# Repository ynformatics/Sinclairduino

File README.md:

# Sinclairduino
See https://ynformatics.com/2021/sinclairduino-vintage-sinclair-calculator-reanimated/

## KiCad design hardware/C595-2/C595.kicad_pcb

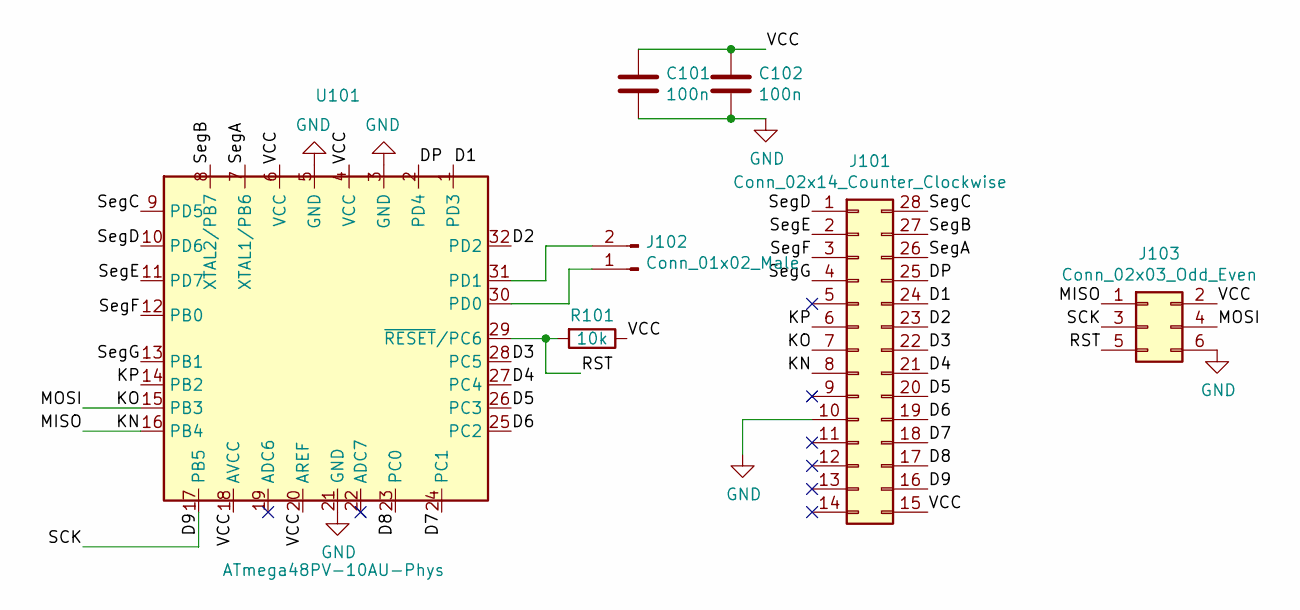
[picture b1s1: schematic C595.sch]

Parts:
C101, C102: 100n; C_0603
J101: Conn_02x14_Counter_Clockwise; DIP-28_W15.24mm
J102: Conn_01x02_Male; C_0805
J103: Conn_02x03_Odd_Even; Pin_Header_Straight_2x03_Pitch1.27mm_SMD
R101: 10k; R_0603
U101: ATmega48PV-10AU-Phys; TQFP-32_7x7mm_Pitch0.8mm

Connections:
/D1: J101.24, U101.1 (PD3)
/D2: J101.23, U101.32 (PD2)
/D3: J101.22, U101.28 (PC5)
/D4: J101.21, U101.27 (PC4)
/D5: J101.20, U101.26 (PC3)
/D6: J101.19, U101.25 (PC2)
/D7: J101.18, U101.24 (PC1)
/D8: J101.17, U101.23 (PC0)
/D9: J101.16, J103.3, U101.17 (PB5)
/DP: J101.25, U101.2 (PD4)
/KN: J101.8, J103.1, U101.16 (PB4)
/KO: J101.7, J103.4, U101.15 (PB3)
/KP: J101.6, U101.14 (PB2)
/RST: J103.5, R101.2, U101.29 (~RESET~/PC6)
/SegA: J101.26, U101.7 (XTAL1/PB6)
/SegB: J101.27, U101.8 (XTAL2/PB7)
/SegC: J101.28, U101.9 (PD5)
/SegD: J101.1, U101.10 (PD6)
/SegE: J101.2, U101.11 (PD7)
/SegF: J101.3, U101.12 (PB0)
/SegG: J101.4, U101.13 (PB1)
/VCC: C101.1, C102.1, J101.15, J103.2, R101.1, U101.4 (VCC), U101.6 (VCC), U101.18 (AVCC), U101.20 (AREF)
unnamed: J102.1, U101.30 (PD0)
unnamed: J102.2, U101.31 (PD1)

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
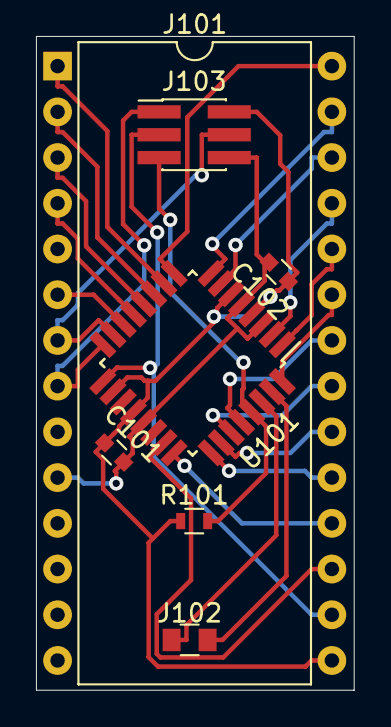
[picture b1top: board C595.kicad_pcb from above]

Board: 2 copper layers, 17.7 x 36.3 mm, 7 parts (0 on the bottom side), 25 nets.
